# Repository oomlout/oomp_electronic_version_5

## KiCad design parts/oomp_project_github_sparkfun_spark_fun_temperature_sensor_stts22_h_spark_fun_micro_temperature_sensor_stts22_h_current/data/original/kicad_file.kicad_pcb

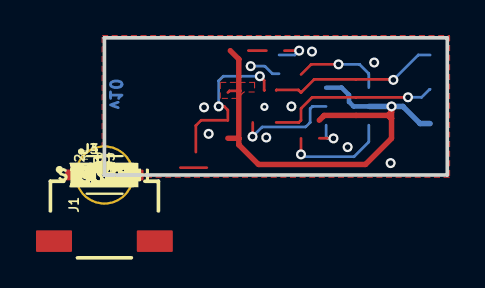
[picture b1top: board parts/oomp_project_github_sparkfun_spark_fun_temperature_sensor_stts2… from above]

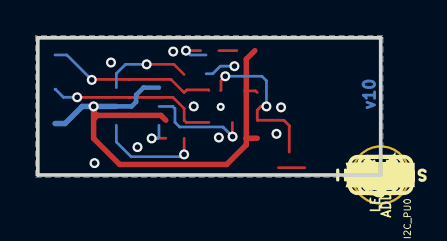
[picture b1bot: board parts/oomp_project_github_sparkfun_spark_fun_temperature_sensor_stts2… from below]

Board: 2 copper layers, 19.1 x 7.6 mm, 40 parts (20 on the bottom side), 11 nets.

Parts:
ADDR0: JUMPER-SMT_3_1-NC_TRACE_SILK; SMT-JUMPER_3_1-NC_TRACE_SILK
C1: 0.1uF; 0402-TIGHT
D1: RED; LED-0402
FD1, FD2: FIDUCIALUFIDUCIAL; FIDUCIAL-MICRO
FID1, FID2: FIDUCIALUFIDUCIAL; FIDUCIAL-MICRO
FRAME1: FRAME-LETTER; CREATIVE_COMMONS
I2C_PU0: S_MODE; SMT-JUMPER_3_2-NC_TRACE_SILK
J1: Qwiic Right Angle; JST04_1MM_RA
J3, J4: 1X01_1MM_NO_SILK
LED0: JUMPER-SMT_2_NC_TRACE_SILK; SMT-JUMPER_2_NC_TRACE_SILK
LOGO1: QWIIC_LOGO_3MM; QWIIC_3MM
LOGO2: OSHW-LOGOMINI; OSHW-LOGO-MINI
LOGO3: SFE_LOGO_NAME_FLAMEBLANK; BLANK
R1, R2, R4: 2.2k; 0402-TIGHT
R3: 10k; 0402-TIGHT
R5: 15K; 0402-TIGHT
STANDOFF1: STAND-OFFTIGHT; STAND-OFF-TIGHT
TP1, TP2, TP3, TP4: TEST-POINT3; PAD.03X.03
U2: STTS22H; UDFN-6L
U$1: #0#4
U$2: #1#4
U$3: #LED#2121
U$4, U$10: #GND#4
U$5, U$6: ##INT##9
U$7, U$8: STTS22H11
U$9: TEMP24
U$11: SENSOR25
U$12: #I2C#4
U$29: SFE_LOGO_FLAME_.1

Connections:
3.3V: ADDR0.1, C1.1, I2C_PU0.2, J1.2, R3.2, R4.2, R5.2, TP3.1, U2.P3
ADDR: ADDR0.2, U2.P4
GND: C1.2, J1.1, J4.1, LED0.1, TP4.1, U2.P5, U2.P7
unnamed: ADDR0.3, R5.1
unnamed: D1.A, R4.1
unnamed: D1.C, LED0.2
unnamed: I2C_PU0.1, R1.2
unnamed: I2C_PU0.3, R2.2
SCL: J1.4, R1.1, TP1.1, U2.P1
SDA: J1.3, R2.1, TP2.1, U2.P6
~INT: J3.1, R3.1, U2.P2

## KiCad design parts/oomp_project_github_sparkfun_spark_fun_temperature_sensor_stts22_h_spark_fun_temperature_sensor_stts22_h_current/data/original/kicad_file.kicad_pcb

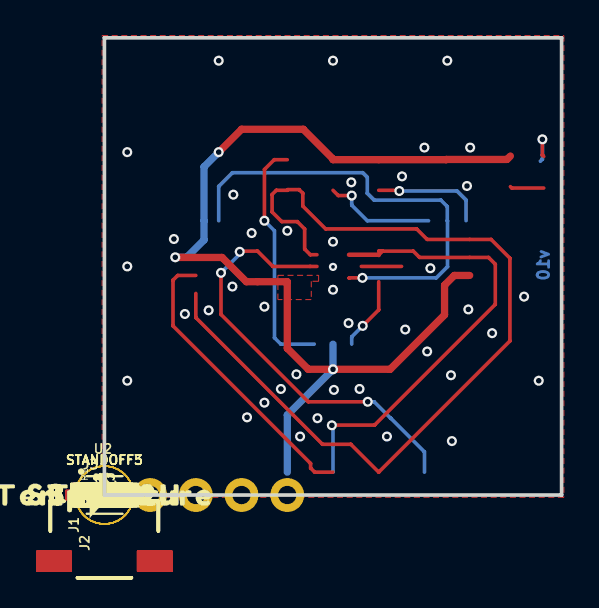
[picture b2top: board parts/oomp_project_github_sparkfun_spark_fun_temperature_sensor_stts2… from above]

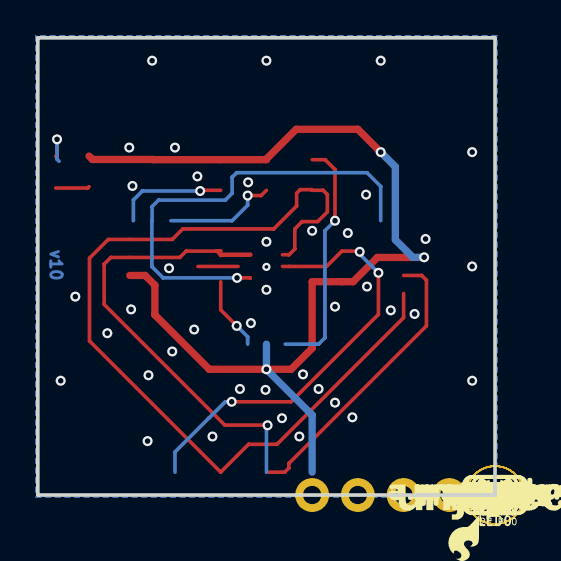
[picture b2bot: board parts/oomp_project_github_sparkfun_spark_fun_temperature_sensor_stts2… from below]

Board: 2 copper layers, 25.4 x 25.4 mm, 56 parts (26 on the bottom side), 12 nets.

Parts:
ADDR0: JUMPER-SMT_3_1-NC_TRACE_SILK; SMT-JUMPER_3_1-NC_TRACE_SILK
ADDR1: JUMPER-SMT_3_NO_SILK; SMT-JUMPER_3_NO_SILK
C1: 0.1uF; 0603
D1: RED; LED-0603
FD1, FD2, FD3, FD4: FIDUCIAL1X2; FIDUCIAL-1X2
FRAME1: FRAME-LETTER; CREATIVE_COMMONS
I2C_PU0: S_MODE; SMT-JUMPER_3_2-NC_TRACE_SILK
J1, J2: QWIIC_RIGHT_ANGLE; JST04_1MM_RA
J3: 1X05_NO_SILK
LED0: JUMPER-SMT_2_NC_TRACE_SILK; SMT-JUMPER_2_NC_TRACE_SILK
LOGO2: OSHW-LOGOMINI; OSHW-LOGO-MINI
LOGO3: SFE_LOGO_NAME_FLAME.1_INCH; SFE_LOGO_NAME_FLAME_.1
LOGO4: QWIIC_LOGO_4MM; QWIIC_4MM
R1, R2: 2.2k; 0603
R3: 10k; 0603
R4: 1k; 0603
R7: 56k; 0603
R8: 15k; 0603
STANDOFF1, STANDOFF2, STANDOFF3, STANDOFF5: STAND-OFFTIGHT; STAND-OFF-TIGHT
U2: STTS22H; UDFN-6L
U$1, U$9: #GND#3
U$2, U$10: #3V3#4
U$3: #SDA#5
U$4: #SCL#4
U$5: #SDA#7
U$6: #ADDR#6
U$7: #SCL#6
U$8: #ADDR1#9
U$11: ##INT##9
U$12: #0X3C#25
U$13: #0X3E#25
U$14: #0X3F#25
U$15: #0X38#25
U$16: #LED#11
U$17, U$23: TEMPERATURE23
U$18: ##INT##6
U$19, U$24: SENSOR24
U$20: SFE_LOGO_FLAME_.1
U$21: PWR9
U$22, U$26: STTS22H21
U$25: #I2C#11
U$27: DEF_ADDR#29
U$28: 0X3C30

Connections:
3.3V: ADDR1.3, C1.1, I2C_PU0.2, J1.2, J2.2, J3.2, R3.2, R4.2, R7.1, R8.2, U2.P3
ADDR: ADDR0.2, ADDR1.2, U2.P4
GND: ADDR1.1, C1.2, J1.1, J2.1, J3.1, LED0.1, U2.P5, U2.P7
unnamed: D1.A, R4.1
unnamed: D1.C, LED0.2
unnamed: ADDR0.3, R8.1
unnamed: I2C_PU0.1, R1.2
unnamed: I2C_PU0.3, R2.2
unnamed: ADDR0.1, R7.2
SCL: J1.4, J2.4, J3.4, R1.1, U2.P1
SDA: J1.3, J2.3, J3.3, R2.1, U2.P6
~INT: J3.5, R3.1, U2.P2

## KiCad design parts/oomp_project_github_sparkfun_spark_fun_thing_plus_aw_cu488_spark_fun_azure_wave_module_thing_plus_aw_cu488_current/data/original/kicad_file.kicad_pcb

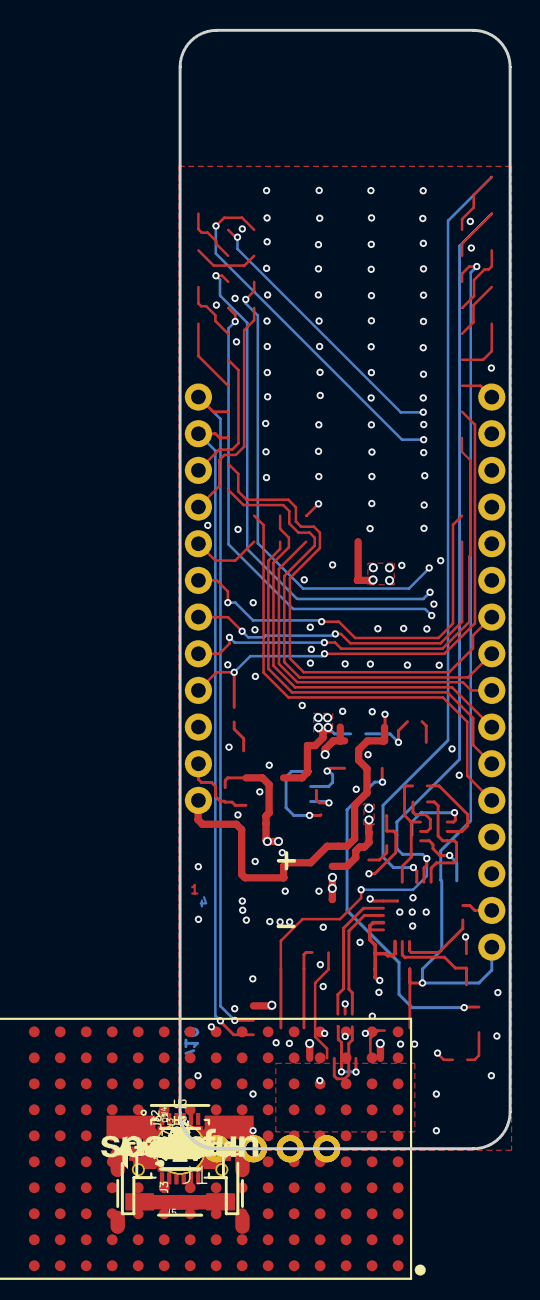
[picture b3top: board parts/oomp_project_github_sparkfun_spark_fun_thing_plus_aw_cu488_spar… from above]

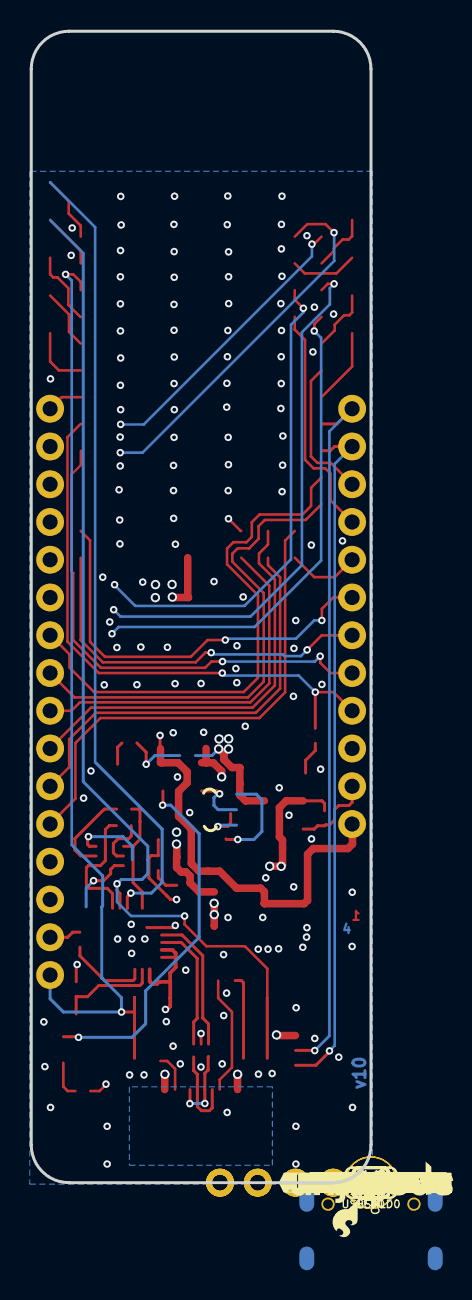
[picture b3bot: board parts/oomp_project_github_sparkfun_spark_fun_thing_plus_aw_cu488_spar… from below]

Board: 4 copper layers, 22.9 x 77.5 mm, 128 parts (57 on the bottom side), 62 nets.

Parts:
C1: 10uF; 0402-TIGHT
C2: 0.1uF; 0402-TIGHT
C3, C6, C19: 4.7uF; 0402-TIGHT
C4: 10uF; 0603
C7, C10: 1.0uF; 0402-TIGHT
CHG0: SMT-JUMPER_3_1-NC_TRACE_SILK
D1: Yellow; LED-0603
D2: 1A/23V/620mV; SOD-323
D3: BLUE; LED-0603
D4: RED; LED-0603
D6: PRTR5V0U2F; SOT886
FD1, FD2, FD3, FD4: FIDUCIALUFIDUCIAL; FIDUCIAL-MICRO
FRAME1: FRAME-LEDGER; CREATIVE_COMMONS
H1, H2: STAND-OFF
J1: THING_PLUS
J2: LiPo; JST-2-SMD
J3: QWIIC_RA; JST04_1MM_RA
J5: USB-C; USB-C-16P-4LAYER-ISOLATED
J6, J7: 1X05_NO_SILK
JP1, JP2: SMT-JUMPER_2_NC_TRACE_SILK
LED0: SMT-JUMPER_2_NC_TRACE_SILK
LOGO1: SFE_LOGO_NAME.1_INCH; SFE_LOGO_NAME_.1
LOGO2: OSHW-LOGOMINI; OSHW-LOGO-MINI
LOGO3: SFE_LOGO_NAME_FLAME.1_INCH; SFE_LOGO_NAME_FLAME_.1
LOGO4: FOUR_LAYER_WARNING
LOGO6: QWIIC_LOGO_4MM; QWIIC_4MM
Q1: 3.1A/30V/105mΩ; SOT23-3
Q2: MBT3904DW1T1; SC70-6
R1, R7, R13, R17, R18: 10k; 0402-TIGHT
R2, R15: 1k; 0402-TIGHT
R3, R4: 4.7k; 0402-TIGHT
R5: 22k; 0402-TIGHT
R6: 2.0k; 0603
R8: 100k; 0402-TIGHT
R9: 33k; 0402-TIGHT
R10: 100; 0402-TIGHT
R11, R12: 5.1k; 0402-TIGHT
S1: SW1/RESET; TACTILE_SWITCH_SMD_4.6X2.8MM
S2: SW2/BOOT; TACTILE_SWITCH_SMD_4.6X2.8MM
U1: AW-CU488; LGA150_AW-CU488
U2: CP210X; QFN24
U3: XC6222B331MR-G; SOT23-5
U4: MCP73831; SOT23-5
U$1: #10#30
U$2: BOOT0
U$3, U$78: CHG0
U$4: #500#0
U$5: #11#30
U$6, U$8: AZUREWAVE0
U$7: 1330
U$9, U$27: AW#CU488_0
U$10, U$62: THING_PLUS_0
U$11: MA0
U$12: #12#30
U$14: #13#30
U$15: #JP1#1
U$16: #0#1
U$18: #A0#30
U$19: #JP2#4
U$20: #USBSHLD#GND#3
U$23: PWR0
U$29: #LED#0
U$32, U$86: #GND#0
U$41: #VUSB#0
U$42: #VBAT#0
U$43: #EN#0
U$45: #3V3#0
U$46: ##RESET##0
U$48: #4#TX1#14
U$49: #3#RX1#14
U$50: #2#POCI#14
U$53: #A1#6
U$54: #A2#6
U$55: #A3#6
U$56: #A4#6
U$57: #A5#6
U$59: ORDERING_INSTRUCTIONS
U$60: #100#0
U$64: #1#PICO#14
U$67: #13#14
U$68: #12#14
U$69: #11#14
U$70: #10#14
U$71: #9#A6#14
U$72: #8#CS#14
U$73: #7#14
U$74: #6#SCL#14
U$75: #5#SDA#14
U$76: #0#SCK#14
U$77: #14#A0#15
U$79: RESET0
U$80: #15#A1#15
U$81: #16#A2#16
U$82: #17#A3#17
U$83: #18#A4#18
U$84: #19#A5#19
U$85: #20#20
U$87: #21#21
U$88: #22#22
U$89: #23#23
U$90: #24#TX#24
U$91: #25#RX#25
U$92: #26#26
U$93: #27#27
U$94: #28#28
U$95: #29#29
USBSHLD0: SMT-JUMPER_2_NC_TRACE_SILK

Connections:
3.3V: C1.1, C2.1, C3.1, C4.1, C10.1, J1.27, J3.2, LED0.1, R1.1, U1.F1, U2.5, U2.6, U2.7, U3.5
CC1: J5.A5, R12.2
CC2: J5.B5, R11.2
CHG: D1.C, U4.1
CHIP_EN: J1.28, JP1.2, S1.1, S1.2, U1.K11
DTR: Q2.1, R17.1, U2.23
EN: J1.11, R8.2, U3.3
GND: C1.2, C2.2, C3.2, C4.2, C6.2, C7.2, C10.2, C19.2, D3.C, D4.C, D6.2, J1.25, J2.1, J3.1, J5.GND, J5.GND2, J7.1, R6.1, R7.1, R9.1, R11.1, R12.1, R13.2, R15.1, S1.3, S1.4, U1.A1, U1.A2, U1.A14, U1.A15, U1.B14, U1.B15, U1.C3, U1.C4, U1.C5, U1.C6, U1.C7, U1.C8, U1.C9, U1.C10, U1.C11, U1.C12, U1.C13, U1.C14, U1.C15, U1.D3, U1.D4, U1.D5, U1.D6, U1.D7, U1.D8, U1.D9, U1.D10, U1.D11, U1.D12, U1.D13, U1.D14, U1.D15, U1.E1, U1.E2, U1.E3, U1.E4, U1.E5, U1.E6, U1.E7, U1.E8, U1.E9, U1.E10, U1.E11, U1.E12, U1.E13, U1.E14, U1.E15, U1.F2, U1.F3, U1.F4, U1.F5, U1.F6, U1.F7, U1.F8, U1.F9, U1.F10, U1.F11, U1.F12, U1.F13, U1.F14, U1.F15, U1.G1, U1.G2, U1.G3, U1.G4, U1.G5, U1.G6, U1.G7, U1.G8, U1.G9, U1.G10, U1.G11, U1.G12, U1.G13, U1.G14, U1.G15, U1.H3, U1.H4, U1.H5, U1.H6, U1.H7, U1.H8, U1.H9, U1.H10, U1.H11, U1.H12, U1.H13, U1.H14, U1.H15, U1.J14, U1.J15, U1.K3, U1.K4, U1.K14, U1.K15, U2.2, U2.PAD, U3.2, U4.2, USBSHLD0.1
LP_UART_RXD: J1.15, U1.B13
LP_UART_TXD: J1.14, U1.A13
unnamed: R1.2, U2.9
unnamed: D3.A, R4.2
unnamed: Q2.5, R17.2
unnamed: R5.1, R9.2, U2.8
unnamed: Q2.2, R18.2
unnamed: JP1.1, Q2.3
unnamed: Q1.1, R10.2
unnamed: R15.2, S2.3, S2.4
unnamed: CHG0.2, U4.5
unnamed: JP2.1, Q2.6
unnamed: CHG0.1, R13.1
unnamed: LED0.2, R2.1
unnamed: CHG0.3, R6.2
unnamed: D4.A, R2.2
unnamed: D6.6, U2.3
unnamed: D6.1, J5.A6, J5.B6
unnamed: D1.A, R3.2
unnamed: D6.4, U2.4
unnamed: D6.3, J5.A7, J5.B7
PA0: J6.1, U1.K8
PA2: J6.3, U1.K10
PA4: J6.2, U1.K9
PA7/UART-LOG-TXD: J6.4, JP2.2, S2.1, S2.2, U1.K12, U2.20
PA8/UART-LOG-RXD: J6.5, U1.K13, U2.21
PA14: J7.2, U1.A12
PA15: J7.3, U1.B12
PA16/PICO: J1.17, U1.A11
PA17/POCI: J1.16, U1.B11
PA18/SCK: J1.18, U1.A10
PA19/CS: J1.4, U1.B10
PA25/SCL: J1.2, J3.4, U1.A5
PA26/SDA: J1.1, J3.3, U1.A6
PA27: J7.4, U1.A9
PA28: J7.5, U1.A7
PA30: J1.3, U1.A8
PB1/A4: J1.20, U1.A3
PB2/A5: J1.19, U1.A4
PB3/A6: J1.5, U1.B1
PB4/A0: J1.24, U1.B2
PB5/A1: J1.23, U1.C1
PB6/A2: J1.22, U1.C2
PB7/A3: J1.21, U1.D1
PB22: J1.7, U1.K1
PB23: J1.6, U1.K2
PB26: J1.8, U1.K5
PB29: J1.9, R4.1, U1.K6
PB31: J1.13, U1.K7
RTS: Q2.4, R18.1, U2.19
USB_SHLD: J5.SHLD1, J5.SHLD2, J5.SHLD3, J5.SHLD4, J5.SHLD5, J5.SHLD6, J5.SHLD7, J5.SHLD8, USBSHLD0.2
VIN: C7.1, D2.C, Q1.2, R8.1, U3.1
V_BATT: C6.1, J1.12, J2.2, Q1.3, U1.D2, U4.3
V_USB: C19.1, D2.A, D6.5, J1.10, J5.VBUS1, J5.VBUS2, R3.1, R5.2, R7.2, R10.1, U4.4

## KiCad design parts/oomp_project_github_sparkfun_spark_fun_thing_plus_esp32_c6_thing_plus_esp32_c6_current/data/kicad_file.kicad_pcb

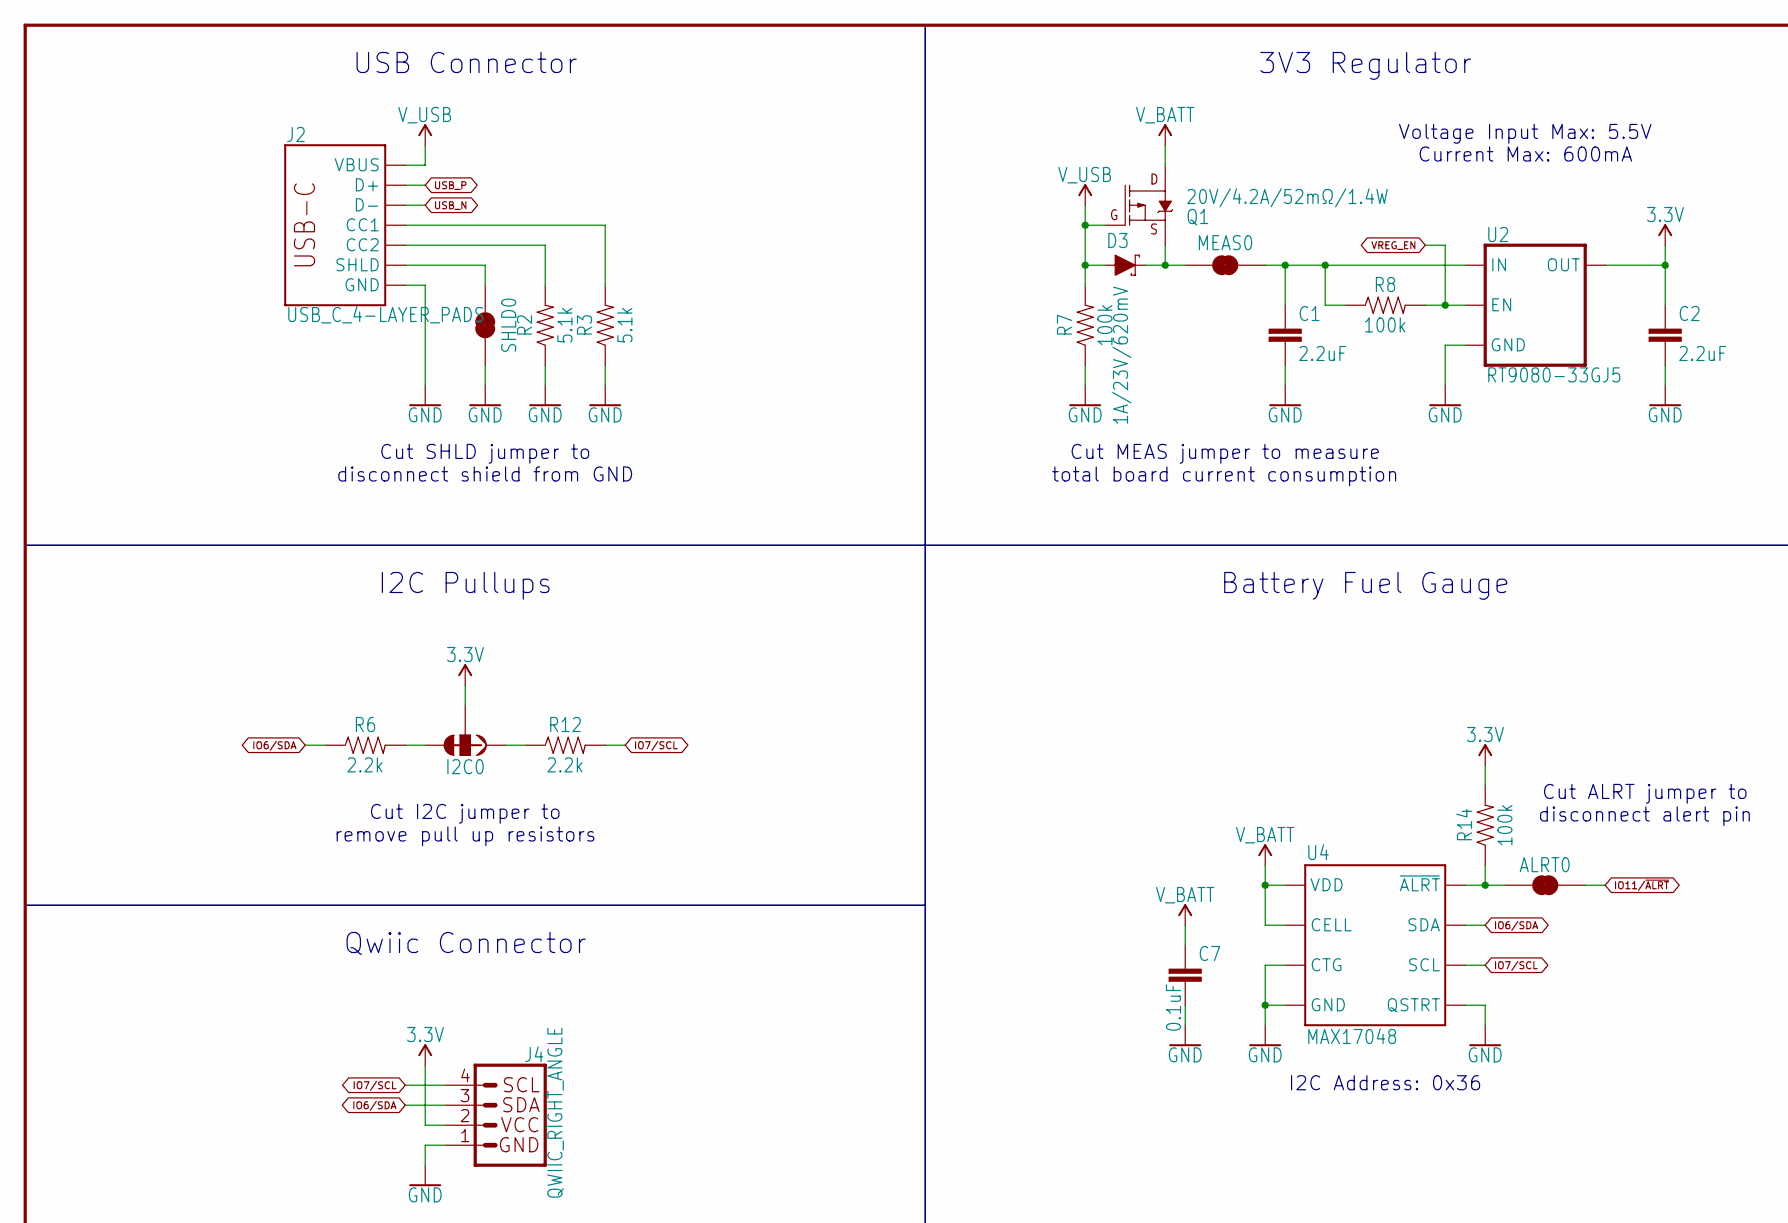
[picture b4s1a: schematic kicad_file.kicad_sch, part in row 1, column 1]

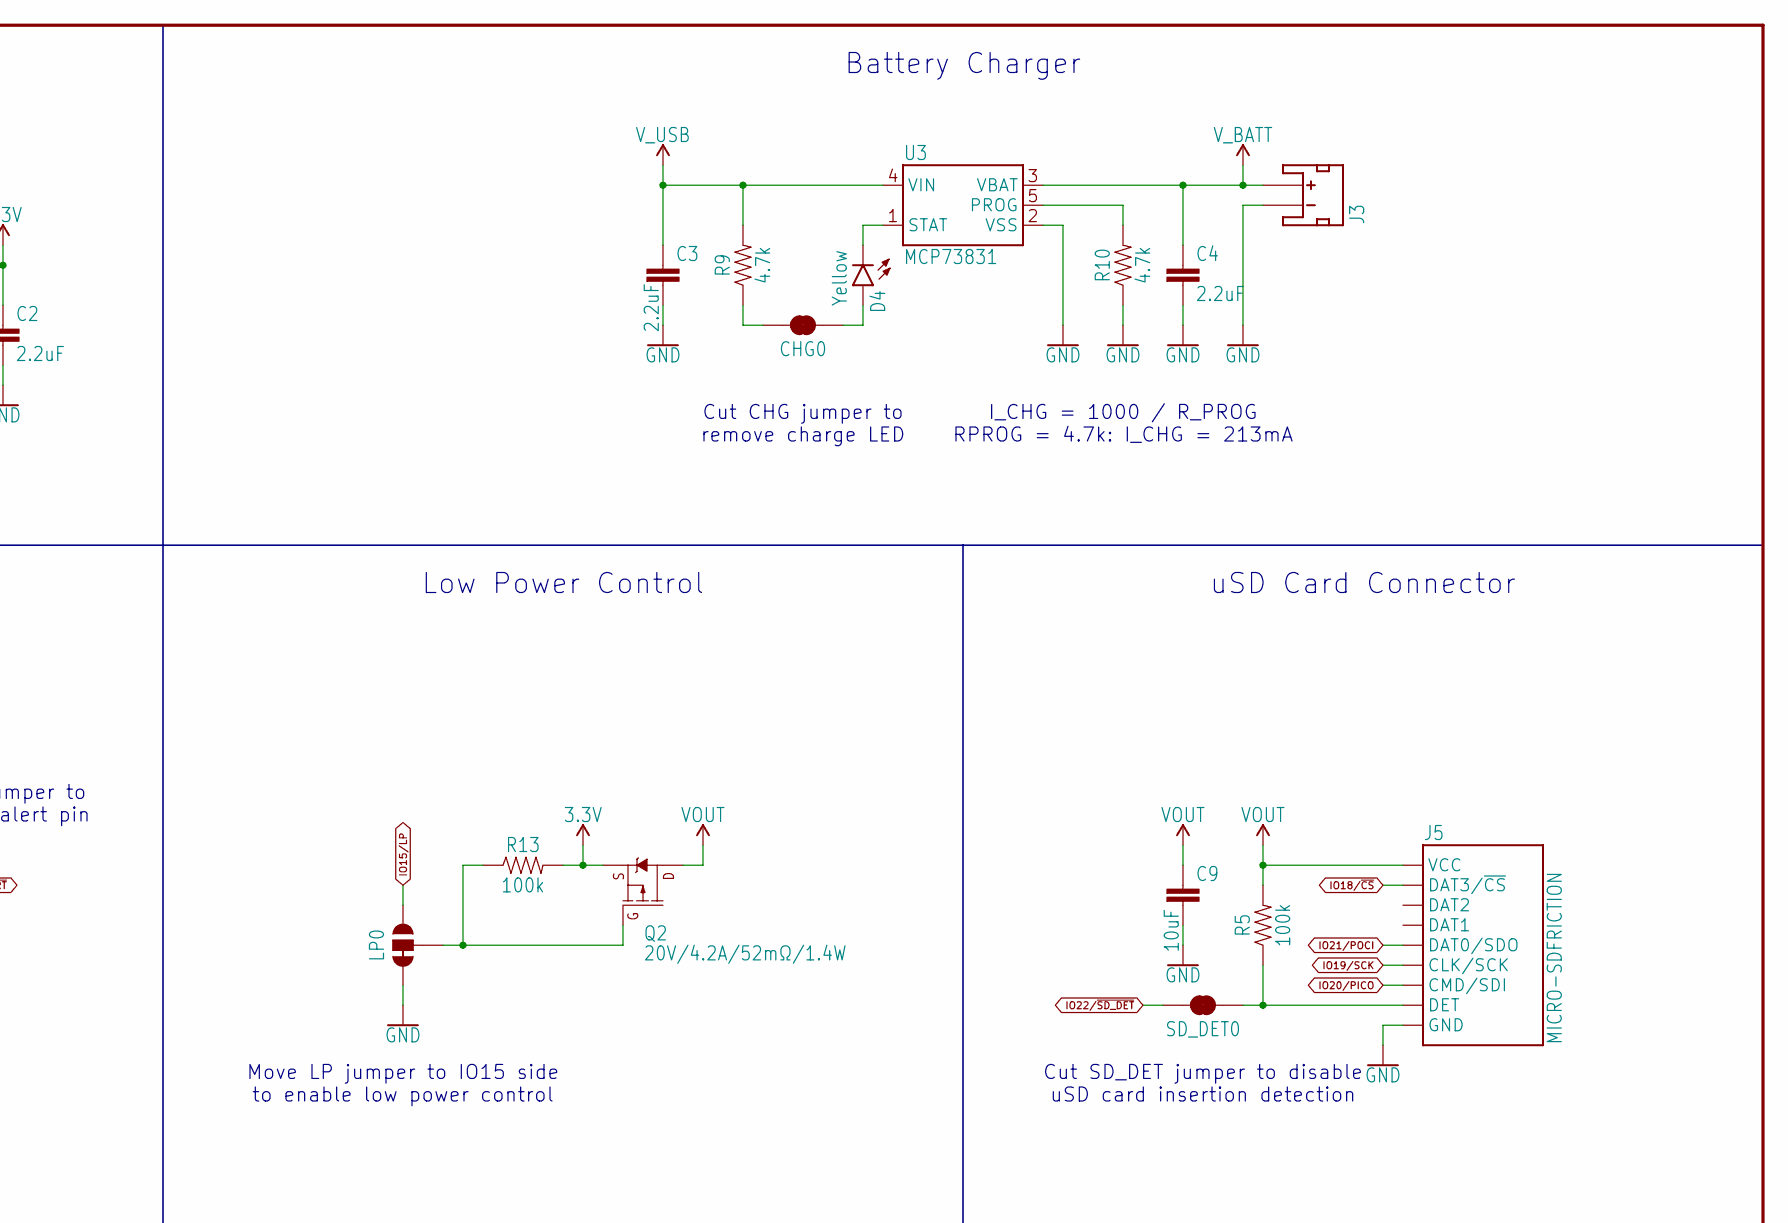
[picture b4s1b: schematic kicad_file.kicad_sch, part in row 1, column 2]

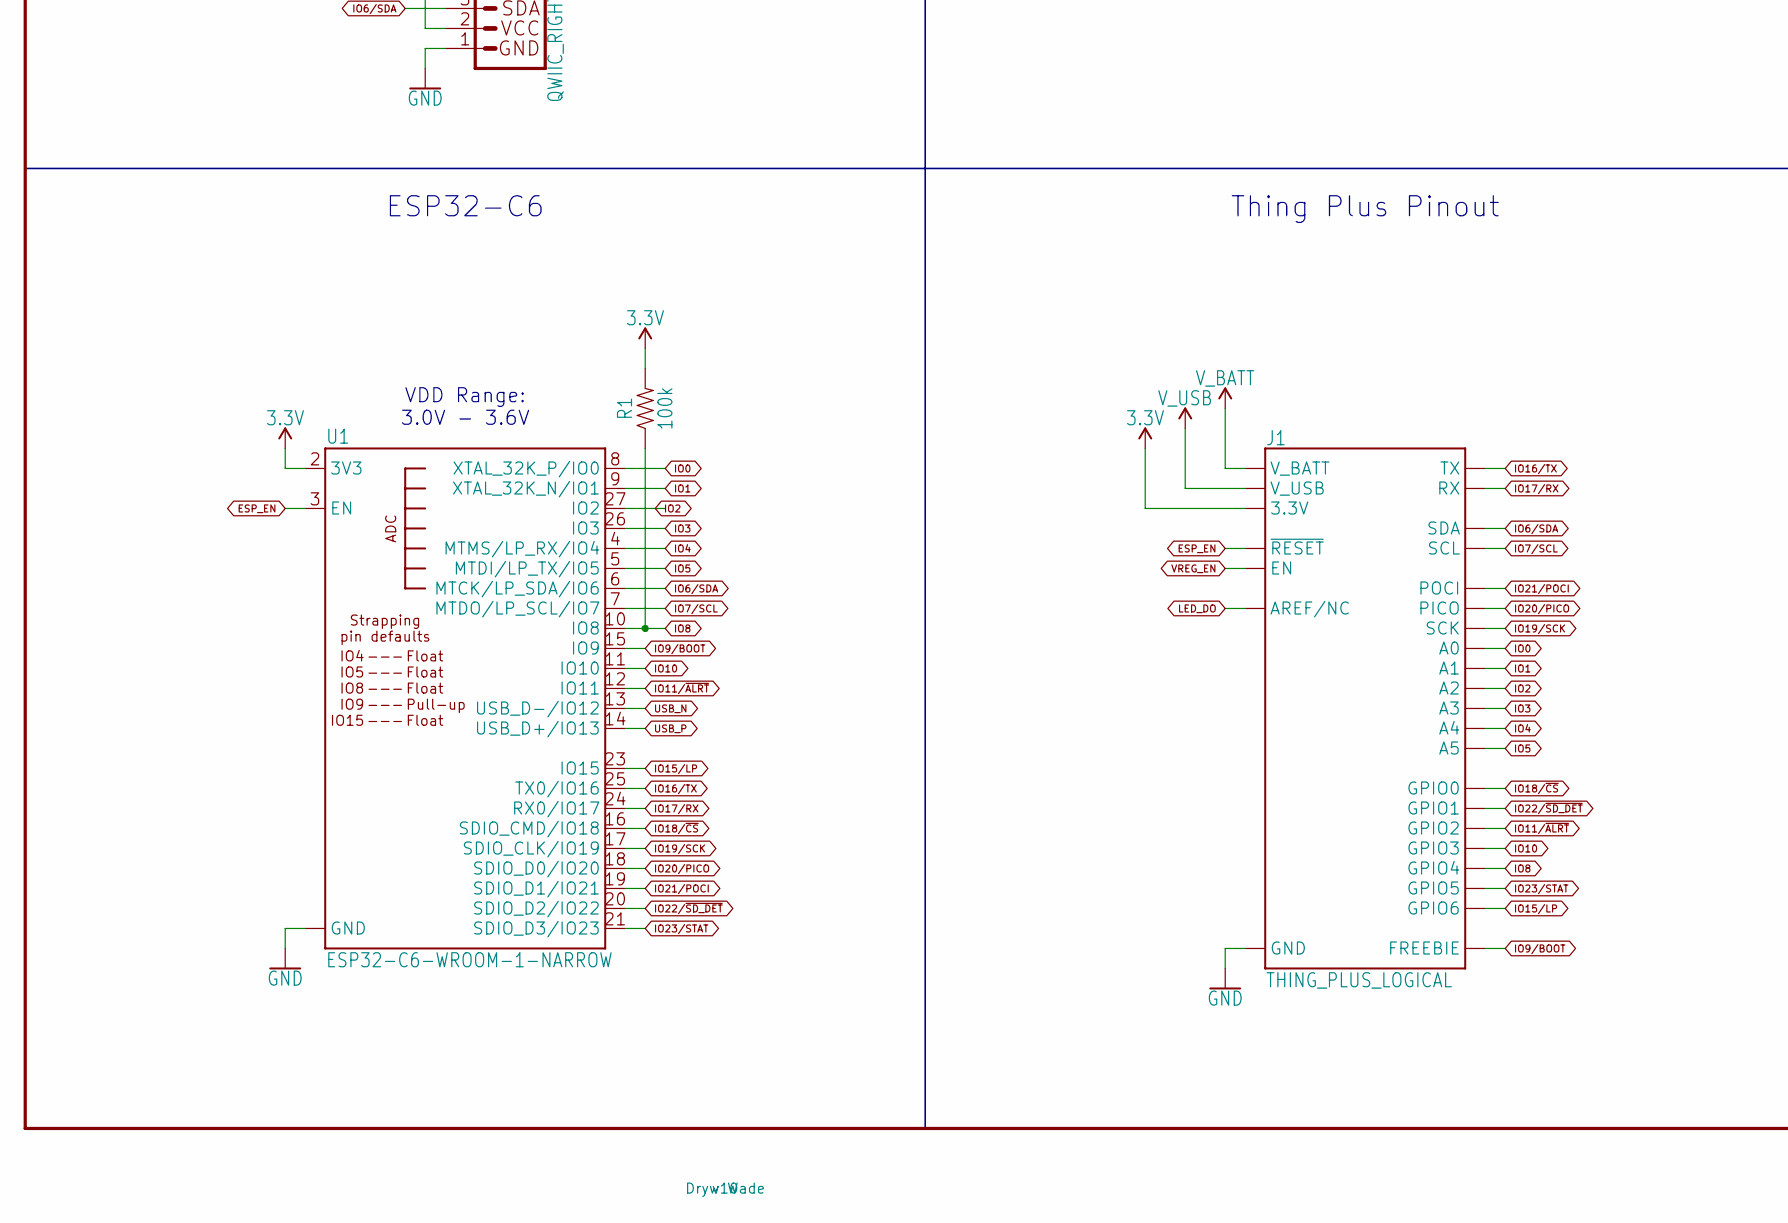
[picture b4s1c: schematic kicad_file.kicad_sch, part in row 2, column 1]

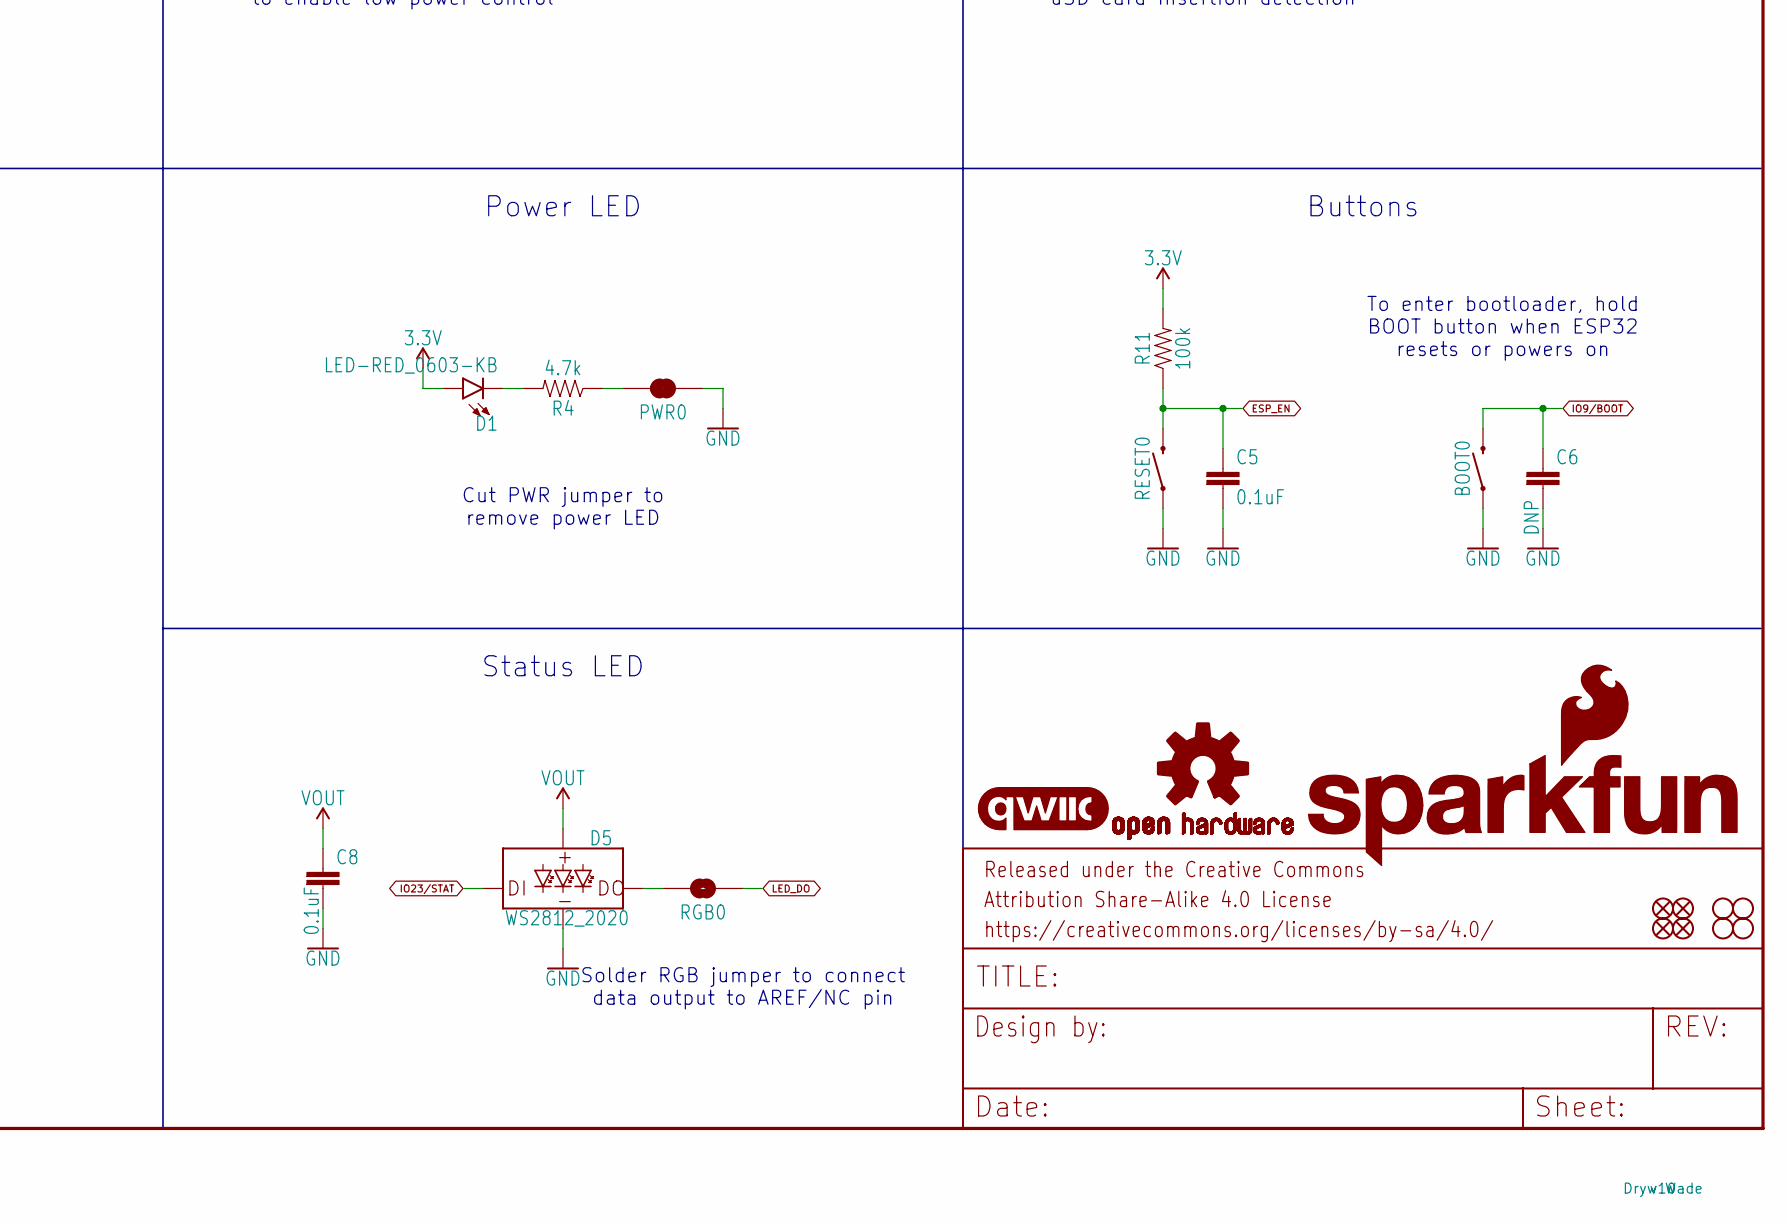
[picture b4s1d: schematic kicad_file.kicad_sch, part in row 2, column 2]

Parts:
ALRT0: JUMPER-SMT_2_NC_TRACE_SILK; SMT-JUMPER_2_NC_TRACE_SILK
BOOT0: MOMENTARY-SWITCH-SPST-SMD-4.6X2.8MM; TACTILE_SWITCH_SMD_4.6X2.8MM
C1, C2, C3, C4: 2.2uF; 0603
C5, C7, C8: 0.1uF; 0603
C6: DNP; 0603
C9: 10uF; 0603
CHG0: JUMPER-SMT_2_NC_TRACE_SILK; SMT-JUMPER_2_NC_TRACE_SILK
D1: LED-RED_0603-KB; LED-0603
D3: 1A/23V/620mV; SOD-323
D4: Yellow; LED-0603
D5: WS2812_2020; WS2812-2020
FD1, FD2, FD3, FD4: FIDUCIALUFIDUCIAL; FIDUCIAL-MICRO
FRAME1: FRAME-LEDGER; CREATIVE_COMMONS
H1, H2, H3, H4: STAND-OFF
I2C0: JUMPER-SMT_3_2-NC_TRACE_SILK; SMT-JUMPER_3_2-NC_TRACE_SILK
J1: THING_PLUS_LOGICAL; THING_PLUS
J2: USB_C_4-LAYER_PADS; USB-C-16P_4LAYER-PADS
J3: JST_2MM_MALE; JST-2-SMD
J4: QWIIC_RIGHT_ANGLE; JST04_1MM_RA
J5: MICRO-SDFRICTION; MICROSD_TINY
LOGO1: SFE_LOGO_NAME_FLAME.1_INCH; SFE_LOGO_NAME_FLAME_.1
LOGO2: QWIIC_LOGO_4MM; QWIIC_4MM
LOGO3: OSHW-LOGOM; OSHW-LOGO-M
LP0: JUMPER-SMT_3_1-NC_TRACE_SILK; SMT-JUMPER_3_1-NC_TRACE_SILK
MEAS0: JUMPER-COMBO_2_NC_TRACE; COMBO-JUMPER_2_NC_TRACE
PWR0: JUMPER-SMT_2_NC_TRACE_SILK; SMT-JUMPER_2_NC_TRACE_SILK
Q1, Q2: 20V/4.2A/52mΩ/1.4W; SOT23-3
R1, R5, R7, R8, R11, R13, R14: 100k; 0603
R2, R3: 5.1k; 0603
R4, R9, R10: 4.7k; 0603
R6, R12: 2.2k; 0603
RESET0: MOMENTARY-SWITCH-SPST-SMD-4.6X2.8MM; TACTILE_SWITCH_SMD_4.6X2.8MM
RGB0: JUMPER-SMT_2_NO_SILK; SMT-JUMPER_2_NO_SILK
SD_DET0: JUMPER-SMT_2_NC_TRACE_SILK; SMT-JUMPER_2_NC_TRACE_SILK
SHLD0: JUMPER-SMT_2_NC_TRACE_SILK; SMT-JUMPER_2_NC_TRACE_SILK
U1: ESP32-C6-WROOM-1-NARROW
U2: RT9080-33GJ5; SOT23-5
U3: MCP73831; SOT23-5
U4: MAX17048; DFN-8

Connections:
3.3V: C2.1, D1.A, I2C0.2, J1.27 (3.3V), J4.2, Q2.2 (S), R1.2, R11.2, R13.2, R14.2, U1.2 (3V3), U2.5 (OUT)
ESP_EN: C5.1, J1.28 (~RESET), R11.1, RESET0.3 (2), RESET0.4 (2), U1.3 (EN)
GND: BOOT0.1, BOOT0.2 (1), C1.2, C2.2, C3.2, C4.2, C5.2, C6.2, C7.2, C8.2, C9.2, D5.GND, J1.25 (GND), J2.GND, J2.GND2 (GND), J3.1 (-), J4.1, J5.6 (GND), J5.GND1 (GND), J5.GND2 (GND), J5.GND3 (GND), J5.GND4 (GND), J5.GND5 (GND), J5.GND6 (GND), LP0.3, PWR0.1, R2.1, R3.1, R7.1, R10.1, RESET0.1, RESET0.2 (1), SHLD0.2, U1.1 (GND), U1.28 (GND), U1.29 (GND), U1.30 (GND), U1.31 (GND), U1.32 (GND), U1.33 (GND), U1.34 (GND), U1.35 (GND), U1.36 (GND), U1.37 (GND), U2.2 (GND), U3.2 (VSS), U4.1 (CTG), U4.4 (GND), U4.6 (QSTRT), U4.9 (GND)
IO0: J1.24 (A0), U1.8 (XTAL_32K_P/IO0)
IO1: J1.23 (A1), U1.9 (XTAL_32K_N/IO1)
IO2: J1.22 (A2), U1.27 (IO2)
IO3: J1.21 (A3), U1.26 (IO3)
IO4: J1.20 (A4), U1.4 (MTMS/LP_RX/IO4)
IO5: J1.19 (A5), U1.5 (MTDI/LP_TX/IO5)
IO6/SDA: J1.1 (SDA), J4.3, R6.1, U1.6 (MTCK/LP_SDA/IO6), U4.8 (SDA)
IO7/SCL: J1.2 (SCL), J4.4, R12.2, U1.7 (MTDO/LP_SCL/IO7), U4.7 (SCL)
IO8: J1.5 (GPIO4), R1.1, U1.10 (IO8)
IO9/BOOT: BOOT0.3 (2), BOOT0.4 (2), C6.1, J1.13 (FREEBIE), U1.15 (IO9)
IO10: J1.6 (GPIO3), U1.11 (IO10)
IO11/~ALRT: ALRT0.2, J1.7 (GPIO2), U1.12 (IO11)
IO15/LP: J1.3 (GPIO6), LP0.1, U1.23 (IO15)
IO16/TX: J1.14 (TX), U1.25 (TX0/IO16)
IO17/RX: J1.15 (RX), U1.24 (RX0/IO17)
IO18/~CS: J1.9 (GPIO0), J5.2 (DAT3/~CS), U1.16 (SDIO_CMD/IO18)
IO19/SCK: J1.18 (SCK), J5.5 (CLK/SCK), U1.17 (SDIO_CLK/IO19)
IO20/PICO: J1.17 (PICO), J5.3 (CMD/SDI), U1.18 (SDIO_D0/IO20)
IO21/POCI: J1.16 (POCI), J5.7 (DAT0/SDO), U1.19 (SDIO_D1/IO21)
IO22/~SD_DET: J1.8 (GPIO1), SD_DET0.2, U1.20 (SDIO_D2/IO22)
IO23/STAT: D5.DI, J1.4 (GPIO5), U1.21 (SDIO_D3/IO23)
LED_DO: J1.26 (AREF/NC), RGB0.1
unnamed: D1.C, R4.2
unnamed: PWR0.2, R4.1
unnamed: J5.9 (DET), R5.1, SD_DET0.1
unnamed: D3.C, MEAS0.1, MEAS0.3 (1), Q1.2 (S)
unnamed: I2C0.3, R6.2
unnamed: I2C0.1, R12.1
unnamed: J2.B5 (CC2), R2.2
unnamed: J2.A5 (CC1), R3.2
unnamed: C1.1, MEAS0.2, MEAS0.4 (2), R8.1, U2.1 (IN)
unnamed: D4.C, U3.1 (STAT)
unnamed: CHG0.1, D4.A
unnamed: CHG0.2, R9.1
unnamed: R10.2, U3.5 (PROG)
unnamed: D5.DO, RGB0.2
unnamed: LP0.2, Q2.1 (G), R13.1
unnamed: ALRT0.1, R14.1, U4.5 (~ALRT)
SHLD: J2.SHLD1 (SHLD), J2.SHLD2 (SHLD), J2.SHLD3 (SHLD), J2.SHLD4 (SHLD), SHLD0.1
USB_N: J2.A7 (D-), J2.B7 (D-), U1.13 (USB_D-/IO12)
USB_P: J2.A6 (D+), J2.B6 (D+), U1.14 (USB_D+/IO13)
VOUT: C8.1, C9.1, D5.VCC, J5.4 (VCC), Q2.3 (D), R5.2
VREG_EN: J1.11 (EN), R8.2, U2.3 (EN)
V_BATT: C4.1, C7.1, J1.12 (V_BATT), J3.2 (+), Q1.3 (D), U3.3 (VBAT), U4.2 (CELL), U4.3 (VDD)
V_USB: C3.1, D3.A, J1.10 (V_USB), J2.VBUS1 (VBUS), J2.VBUS2 (VBUS), Q1.1 (G), R7.2, R9.2, U3.4 (VIN)

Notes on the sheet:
Battery Fuel Gauge
Cut SHLD jumper to disconnect shield from GND
I_CHG = 1000 / R_PROG RPROG = 4.7k: I_CHG = 213mA
3V3 Regulator
Qwiic Connector
To enter bootloader, hold BOOT button when ESP32 resets or powers on
I2C Address: 0x36
Cut PWR jumper to remove power LED
Low Power Control
Power LED
Cut ALRT jumper to disconnect alert pin
I2C Pullups
Battery Charger
Buttons
Cut CHG jumper to remove charge LED
Cut I2C jumper to remove pull up resistors
Status LED
VDD Range: 3.0V - 3.6V
ESP32-C6
Move LP jumper to IO15 side to enable low power control
USB Connector
uSD Card Connector
Thing Plus Pinout
Voltage Input Max: 5.5V Current Max: 600mA
Cut SD_DET jumper to disable uSD card insertion detection
Cut MEAS jumper to measure total board current consumption
Solder RGB jumper to connect data output to AREF/NC pin

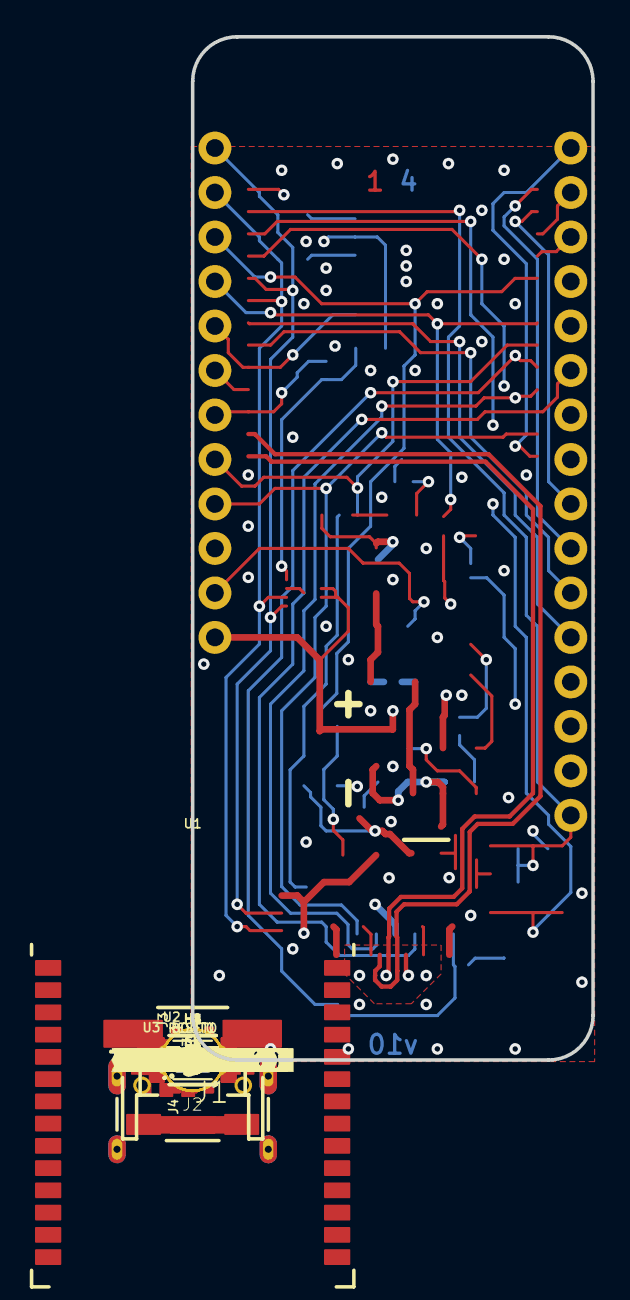
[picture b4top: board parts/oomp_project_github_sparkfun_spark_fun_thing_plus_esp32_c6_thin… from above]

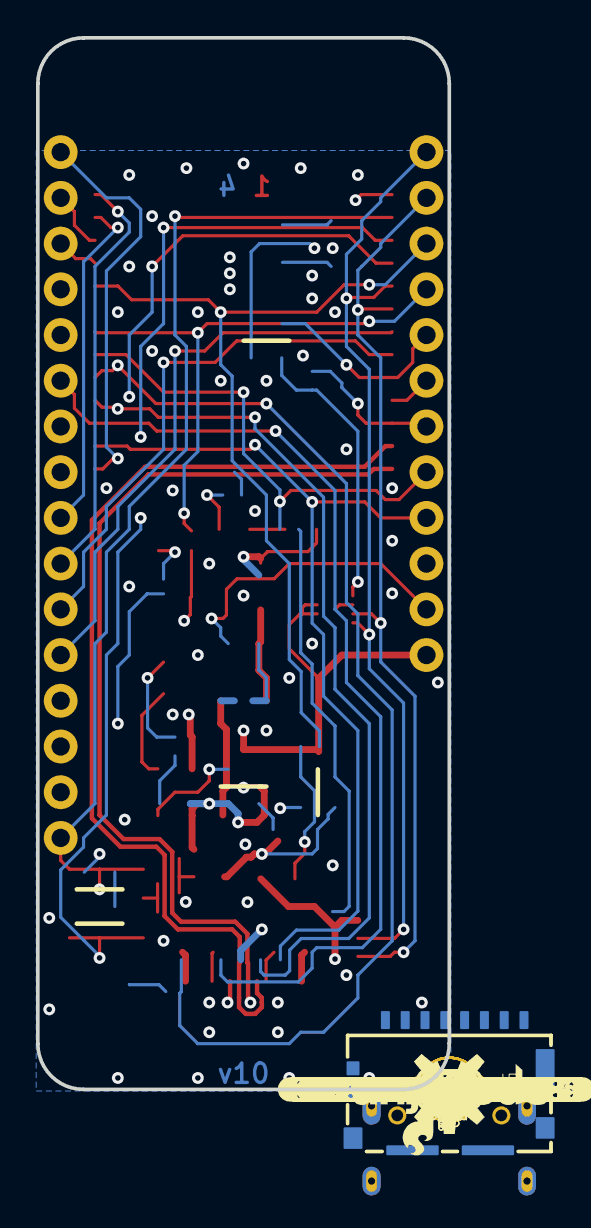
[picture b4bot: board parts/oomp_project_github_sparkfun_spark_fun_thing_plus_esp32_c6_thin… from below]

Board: 4 copper layers, 22.9 x 58.4 mm, 125 parts (69 on the bottom side), 48 nets.

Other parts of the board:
U$1: #SHLD#0
U$2: #I�C#0
U$3: #_IO18#0
U$4: #_VUSB#0
U$5: #_VBAT#0
U$6: #_EN#0
U$7: #IO3_#0
U$8: #IO2_#0
U$9: #IO1_#0
U$10: #IO0_#0
U$11: #GND_#0
U$12: #3V3_#0
U$13, U$37: ##RST#_#0
U$14: #SDA#IO6_#0
U$15: #SCL#IO7_#0
U$16: #_IO21#POCI#0
U$17: #LP#0
U$18: #IO8_#0
U$19: #IO10_#0
U$20: #IO11_#0
U$21: #_IO19#SCK#0
U$22: #IO18_#0
U$23: #_IO9#0
U$24: #_IO16#TX#0
U$25: #_IO17#RX#0
U$26: #_IO20#PICO#0
U$27: #IO15#0
U$28: #ALRT#0
U$29: #_IO5#0
U$30: #_IO4#0
U$31: #_IO3#0
U$32: #_IO2#0
U$33: #_IO1#0
U$34: #_IO0#0
U$35: #_GND#0
U$36: #_3V3#0
U$38: #VUSB_#0
U$39: #VBAT_#0
U$40: #EN_#0
U$41: #SD_DET#0
U$42: BOOT0
U$43: RST0
U$44: IO90
U$45, U$47: THING_PLUS0
U$46, U$48: ESP32#C60
U$49, U$50: #MEAS#0
U$51: #CHG#0
U$52: #PWR#0
U$53: PWR0
U$54: CHG0
U$55: STAT0
U$56: #RGB#0
U$57: ORDERING_INSTRUCTIONS
U$58: #RGB_#0
U$59: #_RGB#0
U$62: IO230
U$63: #G#0
U$64: #IO23_#0
U$65: #IO15_#0
U$66: #IO22_#0

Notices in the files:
parts/oomp_project_github_sparkfun_spark_fun_thing_plus_esp32_c6_thing_plus_esp32_c6_current/data/kicad_file.kicad_sch:
Released under the Creative Commons
https://creativecommons.org/licenses/by-sa/4.0
parts and their libraries:
Released under the Creative Commons Attribution Share-Alike 4.0 License
